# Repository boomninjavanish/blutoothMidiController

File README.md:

# portaMid

[Click to view video of portaMid in use.](https://vimeo.com/428870643)

[Click here to download the manual.](https://github.com/boomninjavanish/portaMid/raw/master/PortaMidUserManual.pdf)

The portaMid keyboard is a MIDI keyboard that works over the Bluetooth Low Energy (BLE) protocol which allows one to control music apps on any  Apple iOS device. The device contains a 500 mAh lithium polymer rechargeable battery which lasts for many hours of use. 

The one octave of piano style keys are soft to the touch but contain tactile feedback so that the user knows when the key has been pressed. Utilizing the octave  keys, the user may lower or raise the octave in which the piano-style keys play. The LED represents the octave selection via different color output.

A removable phone mount allows for use on the go for different sizes of iPhone. In fact, every iPhone since the 4S is supported by the device. Most music apps support MIDI over BLE natively and connect to the portaMid with no configuration required: just connect and use. An example of set-up with the GarageBand app may be found in the user manual.

## Motivation
I chose to create a portable MIDI controller that will allow one to dock a phone and use like a gaming controller. Often, I create music on train trips using my phone and hate inputting notes on the tiny keyboards presented on screen.

## Creation
### Board
A circuit board was designed using KiCAD and is centered around the Adafruit Feather 32u4 Bluefruit LE development microcontroller. The PCB design may be sent to a company such as OSH Park or PCB Way to be printed. The following is a bill of materials for the project (sans circuit board and case):

QTY | Part
---- | ------
1 | Adafruit Feather 32u4 Bluefruit LE Microcontroller
1 | Microchip MCP2307 I2C I/O expander (SPDIP)
1 | Adafruit NeoPixel Through-Hole 5mm LED
13 | 12mm tactile switches
3 |  5mm tactile switches
1 | 100nF ceramic capacitor
1 | 2mm DPDT surface mounted slide switch (DigiKey PN: 401-2002-1-ND)
1 | 1K SMD 1206 resistor
2 | 4.7K SMD 1206 resistor
1 | 3.7V/500mAh Lithium Ion Polymer Battery with 2-pin JST-PH connector

### Case
The final case was modeled in Fusion 360 and was designed to accept an existing phone mount that was found in [Thingiverse](https://www.thingiverse.com/thing:1313336). In order to ensure that the dimensions were correct, the board was exported from KiCAD as a STEP file. Other components such as switches, USB ports, and LEDs were imported into Fusion from a website called [GrabCAD](https://grabcad.com). This website is a community website similar to Thingiverse, but contains mostly engineering components. 

I printed the buttons in NinjaFlex 85A TPU,  which leaves the buttons tactile but feeling soft and reduces noise. The phone clamp connects to the case utilizing a ball joint which allows the keyboard to be used without the phone attached.

The side of the case contains an indentation that allows a USB micro cable to be plugged into the Adafruit feather for charging. The charging LED is visible through one hole near the port and a programmable LED is visible through another.

## User Feedback
For testing, the portaMid was given to two people for a week each. The following is the feedback from the first person:

>*I love the PortaMid!! As a musician who uses midi for all of my projects, it’s so convenient to be able to have an external midi controller. Especially because it’s so portable! I can easily fit it into my purse or backpack and use it wherever I go, train, bus, or at home. I also really love the design, the PortaMid looks as fun as it is to use. The buttons are accessible and labeled to help easily find the functions. I can’t wait to have a PortaMid of my own!*

The second person had the following to say:
>- *Good size to hold*
>- *Clear and simple user manual*
>- *LOVE the color change for different octaves- that was very useful*
>- *Bluetooth easy to set up*
>- *It only took me 10-15 min to get the hang of it and start playing melodies*
>- *I was really excited about the product, and it was more fun to use than I thought it would be*
>- *Thank you for letting me test it!*

## Improvements and Future Work
Going forward, further refinements to the device will be made. For example, it would be nice to have buttons that have the tactile feeling but are less difficult to press and create less noise. Research needs to be done on what could replace the standard tactile buttons with something that is better. In addition, it would be nice to have some velocity sensitive keys for playing more than one dynamic.

In addition, I will need to create a circuit that can poll the battery level at intervals in order to indicate the current charge level or if the battery is dying.

The stand could use a wing-nut to allow the user to adjust the tension so as to keep the unit in the proper position when in use. Also, it would allow for ease of removing the stand entirely.

While using the product, I found myself gripping the device like a game-pad. I had the thought of incorporating shoulder buttons which could be used for modulation, pitch bend, after-touch pressure, etc. 

I envision an entire line of these being made with different properties. For example it would be nice to have a version that mimics the Moog style ribbons, or another version that is a mini sequencer. It would only take finding different sensors or button layouts and incorporating them into the current design for a completely different type of interface.

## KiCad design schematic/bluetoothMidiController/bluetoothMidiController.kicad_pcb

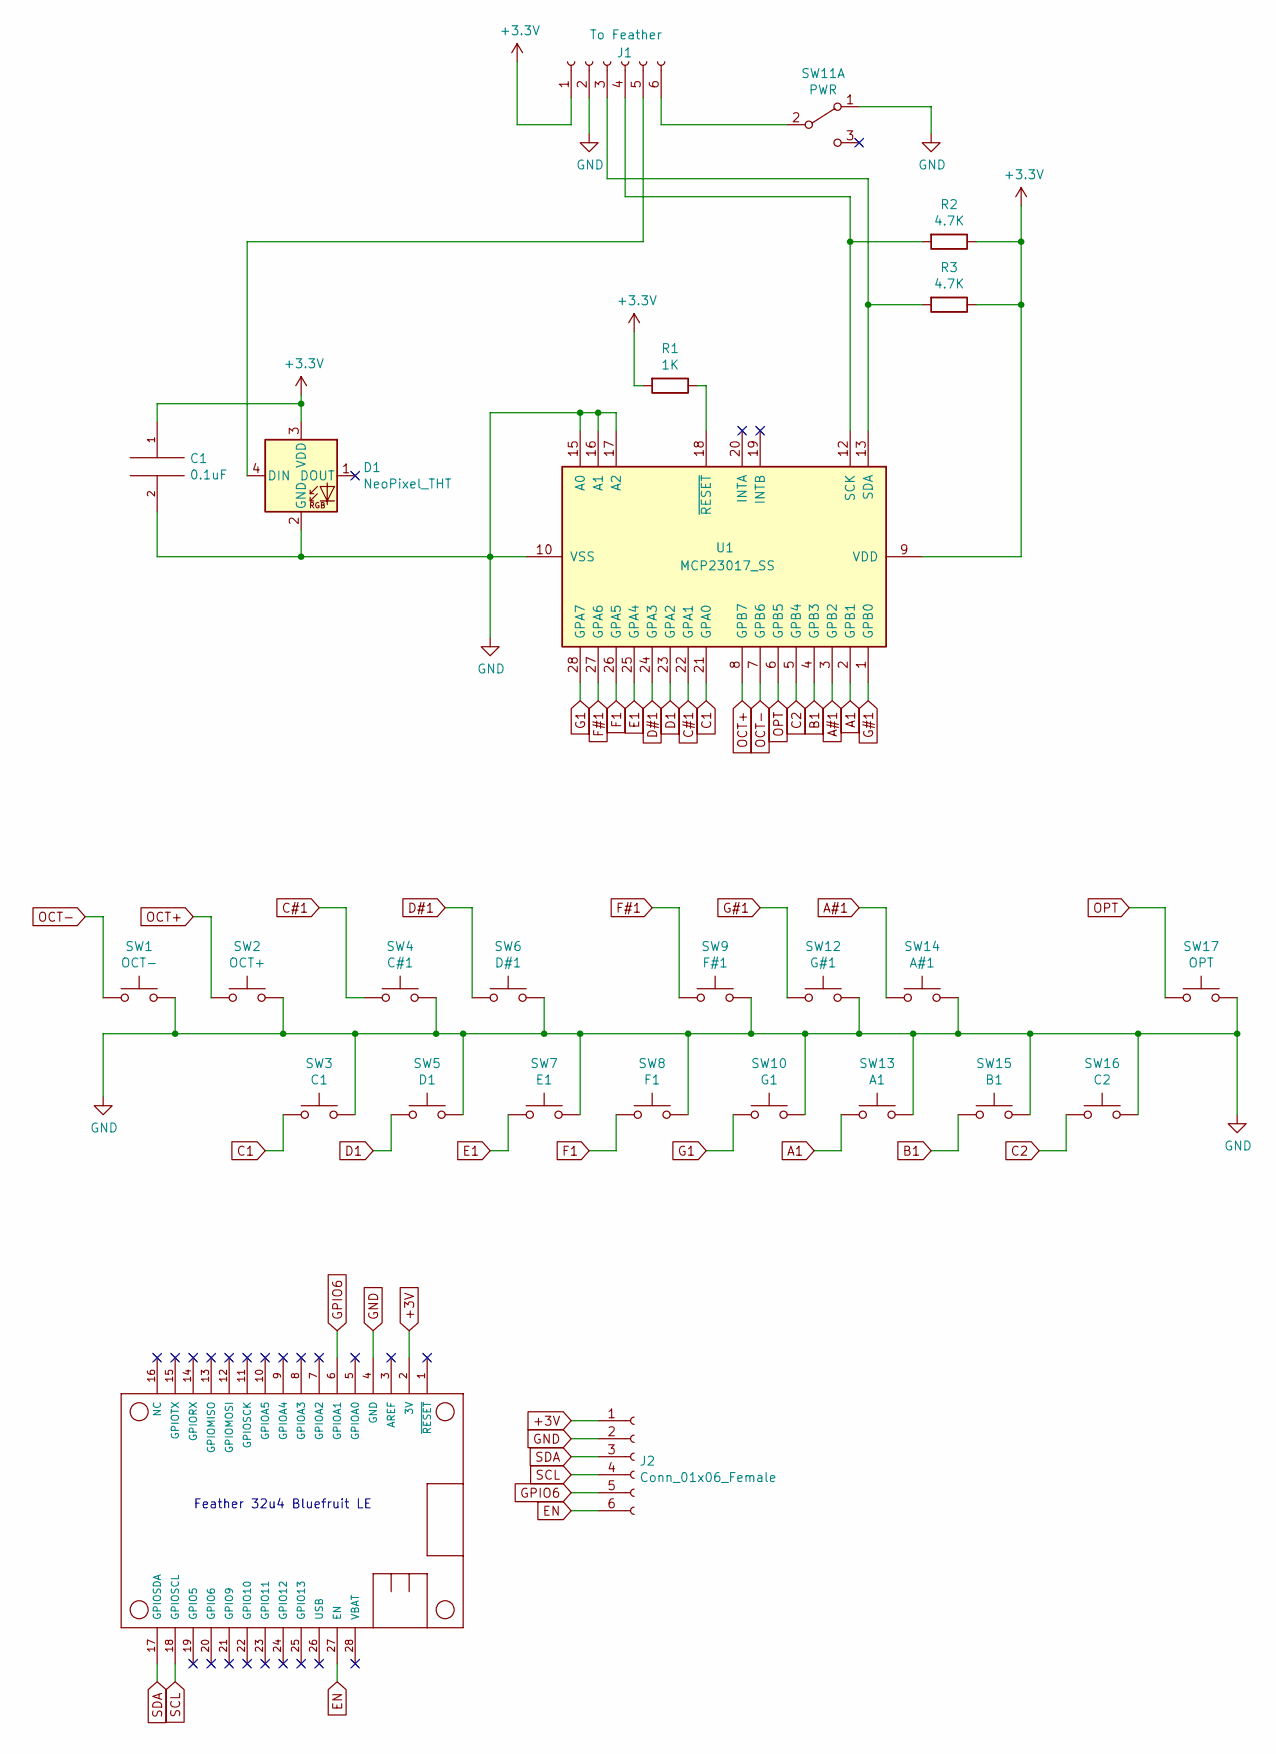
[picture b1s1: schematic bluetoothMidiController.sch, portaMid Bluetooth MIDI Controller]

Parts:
C1: 0.1uF; C_Disc_D3.0mm_W1.6mm_P2.50mm
D1: NeoPixel_THT; LED_D5.0mm-4_RGB_Wide_Pins
J1: To Feather; SolderWire-0.5sqmm_1x06_P4.8mm_D0.9mm_OD2.3mm
J2: Conn_01x06_Female
MS1: FEATHERWING
R1: 1K; R_1206_3216Metric_Pad1.42x1.75mm_HandSolder
R2, R3: 4.7K; R_1206_3216Metric_Pad1.42x1.75mm_HandSolder
SW1: OCT-; SW_PUSH_6mm
SW2: OCT+; SW_PUSH_6mm
SW3: C1; SW_PUSH-12mm
SW4: C#1; SW_PUSH-12mm
SW5: D1; SW_PUSH-12mm
SW6: D#1; SW_PUSH-12mm
SW7: E1; SW_PUSH-12mm
SW8: F1; SW_PUSH-12mm
SW9: F#1; SW_PUSH-12mm
SW10: G1; SW_PUSH-12mm
SW11: PWR; SW_SMD_DPDT_JS202011SCQN
SW12: G#1; SW_PUSH-12mm
SW13: A1; SW_PUSH-12mm
SW14: A#1; SW_PUSH-12mm
SW15: B1; SW_PUSH-12mm
SW16: C2; SW_PUSH-12mm
SW17: OPT; SW_PUSH_6mm
U1: MCP23017_SS; DIP-28_W7.62mm

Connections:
+3V3: C1.1, D1.3 (VDD), J1.1, R1.2, R2.1, R3.1, U1.9 (VDD)
A1: SW13.1, U1.2 (GPB1)
A#1: SW14.1, U1.3 (GPB2)
B1: SW15.1, U1.4 (GPB3)
C1: SW3.1, U1.21 (GPA0)
C2: SW16.1, U1.5 (GPB4)
C#1: SW4.1, U1.22 (GPA1)
D1: SW5.1, U1.23 (GPA2)
D#1: SW6.1, U1.24 (GPA3)
E1: SW7.1, U1.25 (GPA4)
F1: SW8.1, U1.26 (GPA5)
F#1: SW9.1, U1.27 (GPA6)
G1: SW10.1, U1.28 (GPA7)
G#1: SW12.1, U1.1 (GPB0)
GND: C1.2, D1.2 (GND), J1.2, SW1.2, SW2.2, SW3.2, SW4.2, SW5.2, SW6.2, SW7.2, SW8.2, SW9.2, SW10.2, SW11.1 (A), SW12.2, SW13.2, SW14.2, SW15.2, SW16.2, SW17.2, U1.10 (VSS), U1.15 (A0), U1.16 (A1), U1.17 (A2)
unnamed: D1.4 (DIN), J1.5
unnamed: J1.3, R3.2, U1.13 (SDA)
unnamed: J1.4, R2.2, U1.12 (SCK)
unnamed: J1.6, SW11.2 (B)
unnamed: J2.1, MS1.2 (3V)
unnamed: J2.2, MS1.4 (GND)
unnamed: J2.3, MS1.17 (GPIOSDA)
unnamed: J2.4, MS1.18 (GPIOSCL)
unnamed: J2.5, MS1.6 (GPIOA1)
unnamed: J2.6, MS1.27 (EN)
unnamed: R1.1, U1.18 (~RESET~)
OCT+: SW2.1, U1.8 (GPB7)
OCT-: SW1.1, U1.7 (GPB6)
OPT: SW17.1, U1.6 (GPB5)

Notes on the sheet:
Feather 32u4 Bluefruit LE

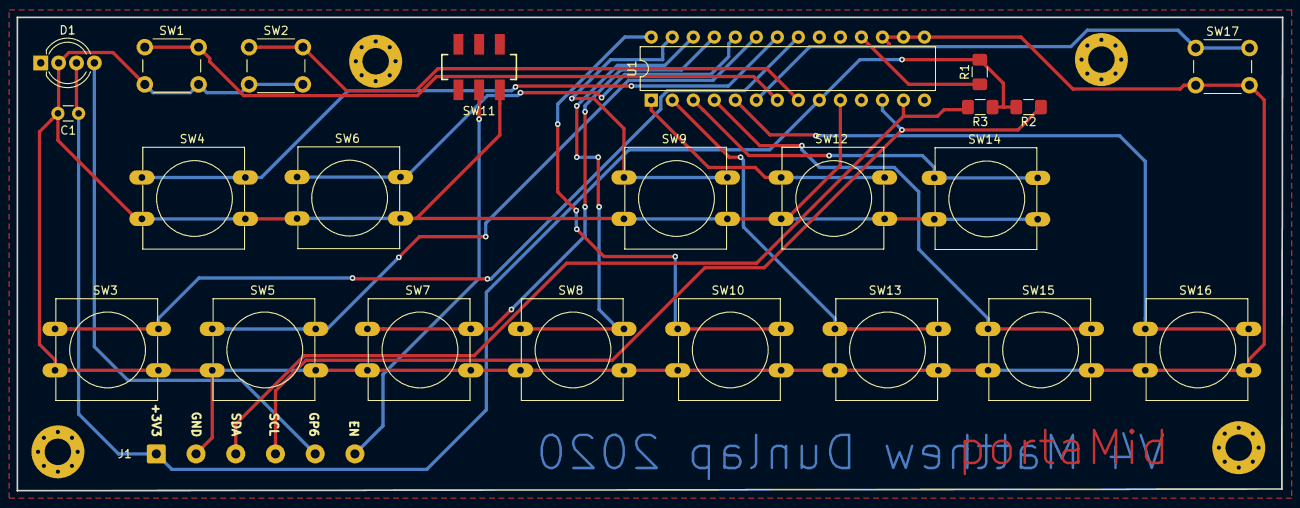
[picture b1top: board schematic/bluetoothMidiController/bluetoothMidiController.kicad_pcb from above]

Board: 2 copper layers, 152.9 x 57.2 mm, 24 parts (0 on the bottom side), 23 nets.

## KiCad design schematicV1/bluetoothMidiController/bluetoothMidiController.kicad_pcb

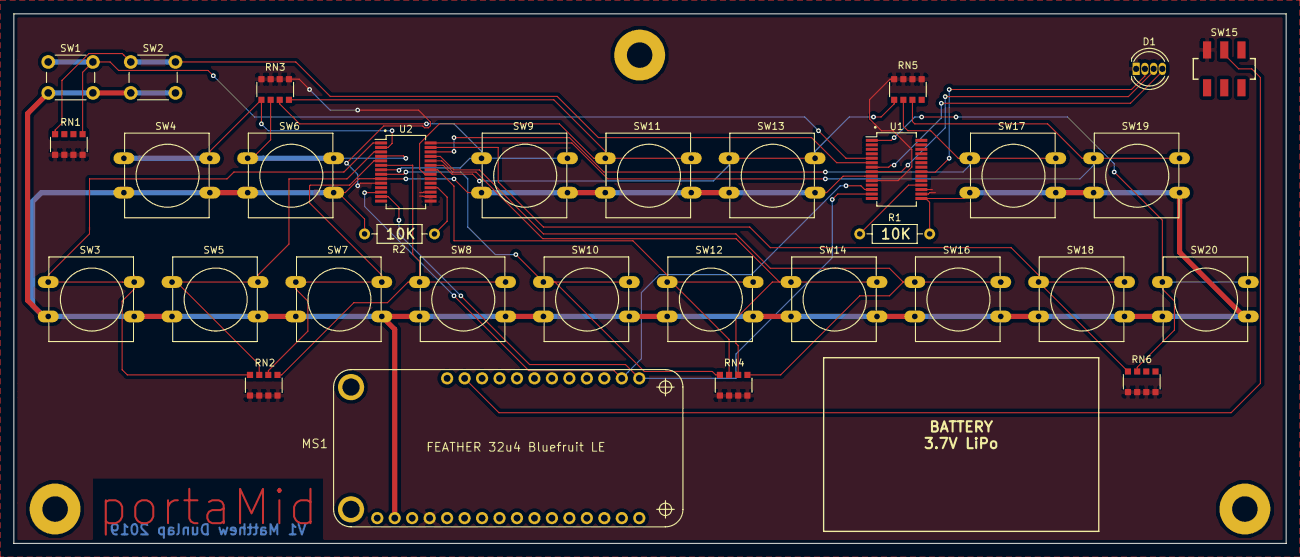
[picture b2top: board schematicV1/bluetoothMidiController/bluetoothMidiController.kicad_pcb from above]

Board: 2 copper layers, 185.0 x 77.0 mm, 32 parts (0 on the bottom side), 29 nets.

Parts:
D1: LED_CRGB; LED_D5.0mm-4_RGB
MS1: FEATHER 32u4 Bluefruit LE; FEATHERWING
R1, R2: 10K; R_Axial_DIN0207_L6.3mm_D2.5mm_P10.16mm_Horizontal
RN1, RN2, RN3, RN4, RN5, RN6: 1K; R_Array_Convex_4x1206
SW1: OCT-; SW_PUSH_6mm
SW2: OCT+; SW_PUSH_6mm
SW3: C1; SW_PUSH-12mm
SW4: C#1; SW_PUSH-12mm
SW5: D1; SW_PUSH-12mm
SW6: D#1; SW_PUSH-12mm
SW7: E1; SW_PUSH-12mm
SW8: F1; SW_PUSH-12mm
SW9: F#1; SW_PUSH-12mm
SW10: G1; SW_PUSH-12mm
SW11: G#1; SW_PUSH-12mm
SW12: A1; SW_PUSH-12mm
SW13: A#1; SW_PUSH-12mm
SW14: B1; SW_PUSH-12mm
SW15: PWR; SW_SMD_DPDT_JS202011SCQN
SW16: C2; SW_PUSH-12mm
SW17: C#2; SW_PUSH-12mm
SW18: D2; SW_PUSH-12mm
SW19: D#2; SW_PUSH-12mm
SW20: E2; SW_PUSH-12mm
U1, U2: MCP23017_SS; SSOP-28_5.3x10.2mm_P0.65mm

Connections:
+3V3: MS1.2, R1.2, R2.1, SW1.2, SW2.2, SW3.2, SW4.2, SW5.2, SW6.2, SW7.2, SW8.2, SW9.2, SW10.2, SW11.2, SW12.2, SW13.2, SW14.2, SW16.2, SW17.2, SW18.2, SW19.2, SW20.2, U1.9, U1.15, U2.9
A1: RN4.7, SW12.1, U2.22
A#1: RN5.1, SW13.1, U2.23
B1: RN4.6, SW14.1, U2.24
C1: RN2.8, SW3.1, U2.1
C2: RN4.5, SW16.1, U2.25
C#1: RN3.1, SW4.1, U2.2
C#2: RN5.2, SW17.1, U2.26
D1: RN2.7, SW5.1, U2.3
D2: RN6.8, SW18.1, U2.27
D#1: RN3.2, SW6.1, U2.4
D#2: RN5.3, SW19.1, U2.28
E1: RN2.6, SW7.1, U2.5
E2: RN6.7, SW20.1, U1.1
F1: RN2.5, SW8.1, U2.6
F#1: RN3.3, SW9.1, U2.7
G1: RN4.8, SW10.1, U2.8
G#1: RN3.4, SW11.1, U2.21
GND: D1.1, MS1.4, RN1.5, RN1.6, RN1.7, RN1.8, RN2.1, RN2.2, RN2.3, RN2.4, RN3.5, RN3.6, RN3.7, RN3.8, RN4.1, RN4.2, RN4.3, RN4.4, RN5.5, RN5.6, RN5.7, RN5.8, RN6.1, RN6.2, RN6.3, RN6.4, SW15.1, U1.10, U1.16, U1.17, U2.10, U2.15, U2.16, U2.17
unnamed: D1.2, U1.21
unnamed: D1.3, U1.8
unnamed: D1.4, U1.7
unnamed: MS1.17, U1.13, U2.13
unnamed: MS1.18, U1.12, U2.12
unnamed: MS1.27, SW15.2
unnamed: R1.1, U1.18
unnamed: R2.2, U2.18
OCT+: RN1.4, SW2.1, U1.6
OCT-: RN1.1, SW1.1, U1.5

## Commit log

2019-02-03 Initial Commit of Code and other files
2019-02-10 Added schemtic and PCB design files.
2019-02-23 Added 3D printed case design
2019-02-23 Added two MCP23017
    Changed the code so it now supports the two MCP23017 chips for I/O. Moved to a different Bounce2 library as a result. Some more work needs to be done to improve speed and reliability of the device. C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
2019-03-02 improved response time
2019-03-04 removed debouncerMCP
    Removed the debouncer in the hopes that the board will be more responsive.
2019-03-08 Reduced to one MCP23017 and Updated wiring on board
    I removed one MCP23017 because the keyboard is reducing in size and the other expander is no longer needed. Also, I discovered that I was wiring the board incorrectly and adjusted the code to reflect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
2019-03-08 Added RGB LED support; started version 2 of board
2019-03-09 completed V2 of the PCB
2019-04-03 Change Board to V3 for DIP version of MCP23017
2019-04-19 Changed the RGB LED to a single 5mm Adafruit Neopixel
2019-04-21 Changed schematic to version 4
    Added pull-up resistors for MCP23017
2019-05-27 added manual
2020-06-14 cleaned up folders and added README.md
2020-06-14 removed extraneous files
2020-06-16 updated PCB to include two 4.7K resisters for I2C bus
2020-06-16 corrected number of 4.7K resistors
2020-06-18 Create LICENSE
